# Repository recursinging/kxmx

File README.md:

# kxmx

kxmx, pronounced "krachmacher", is a moniker connecting a heterogenous, but loosely coupled group of projects, mostly having to do with audio and music.  In sum, the components should form a sort of musical instrument, or maybe better a "rig", but I don't consider that a design goal.

## Motivation

I'm in a band.  Actually, two.  I sing, not particularly good, but it's fun, and I enjoy making music.  What I enjoy more though, is learning about, and tinkering with the technical aspects of making music. Because of this, actual music composition or lyric writing can be regularly postponed for technical reasons.

Easily bored, I like to keep a diverse set of projects going parallel.  These projects may lie dormant for months. I work, I have kids, I don't have much me time.

## Parts, moving or otherwise

Here's a list of projects either already underway, or things I'd like to do eventually...

### kxmx_hirn

A robust, portable (but damn heavy) [DJ case](https://www.magma-bags.de/multi-format-workstation-xl-plus.html) which I gutted and hacked to support Eurorack modules with 350 HU of capacity.  Built in are +19v, +12v, -12v, and +5v power supplies. A lot of the other kxmx components are in, or destined for this case, but since there are a number of ideas I'd like to explore with the case itself, making it a project in it's own right.

### kxmx_erack

A set of basic PCB templates for Eurorack modules which leverage the wonder of exceptionally cheap chinese fabrication.

### [kxmx_ruitar](https://github.com/recursinging/ruitar)

A guitar shaped MIDI/OSC controller, and hopefully someday, a standalone synthesizer.  I wanted to make something tactile to control parameters with, but in a more familiar way (to me) Being more comfortable on the guitar than the keyboard, the ruitar is the logical solution.

### kxmx_trig

A piezo drum trigger module, intended to collect and send a few drum events to kxmx_hirn where they can be abused.

### kxmx_vl2

The brain of a lobotomized TC Helicon [Voice Live 2](https://www.tc-helicon.com/Categories/Tchelicon/Vocal/Multi-Effects/VOICELIVE-2/p/P0CMC) which has been converted from a foot pedal to Eurorack format mounted in kxmx_hirn

### kxmx_4x4

A 4x4 VCA matrix mixer based on SSM2164 clones, and has a modular design:

* *kxmx_4x4_core* - The 16 x2164 voltage control ports of the core module are intentionally broken out to the edge of the board. This allows for pluggable control boards to control the gain of the matrix however they want.  
* *kxmx_4x4_control_esp32* - This module controls the gain of the core using an Expressif ESP32 MCU which has WiFi and Bluetooth out of the box.  This module will make the mixer gain levels remotely controllable via MIDI or OSC.
* *kxmx_4x4_control_cv* - This module allows the gain of the core to be controlled by TRS jack at Eurorack CV levels.

### [kxmx_dsp](https://github.com/recursinging/kxmx_dsp)

Experiments with DSP concepts and algorithms

### [kxmx_trestle](https://github.com/recursinging/kxmx_trestle)

A bi-directional OSC SLIP encoded serial to UDP bridge.

## Licenses

I'll try to be consistent:

* Standalone software/firmware is [LGPLv3](https://www.gnu.org/licenses/lgpl-3.0.en.html)
* Software libraries are [MIT](https://opensource.org/licenses/MIT)
* Hardware/Media is [CC-BY-NC-SA 3.0](https://creativecommons.org/licenses/by-nc-sa/3.0/)

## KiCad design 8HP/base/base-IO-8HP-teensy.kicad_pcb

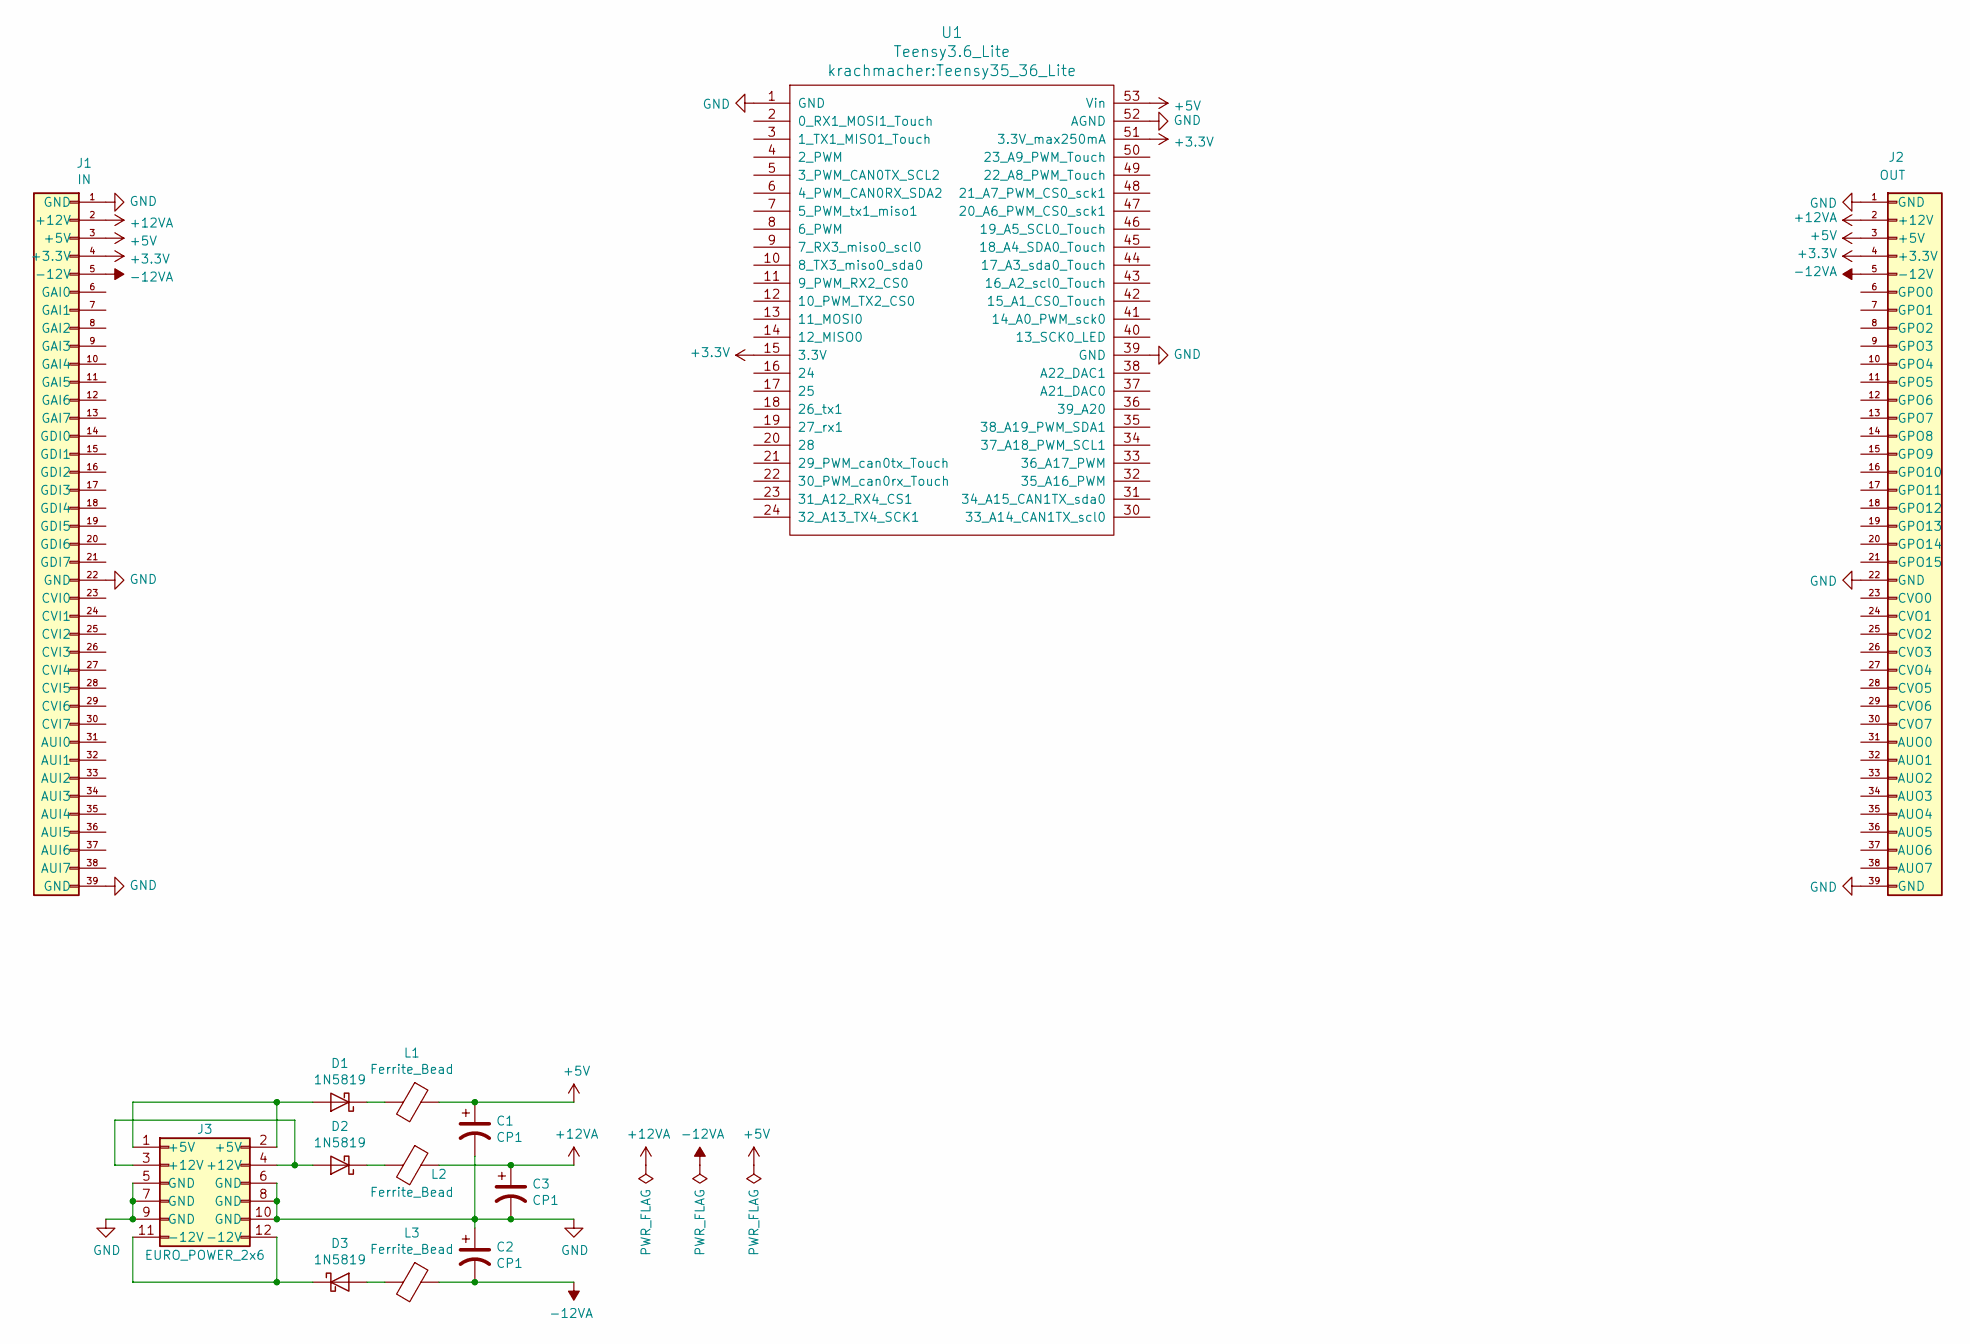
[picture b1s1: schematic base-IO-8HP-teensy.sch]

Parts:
C1, C2, C3: CP1; CP_Elec_4x5.8
D1, D2, D3: 1N5819; D_SOD-123
J1: IN; PinSocket39
J2: OUT; PinSocket39
J3: EURO_POWER_2x6; Pin_Header_Straight_2x06_Pitch2.54mm
L1, L2, L3: Ferrite_Bead; L_0603
U1: Teensy3.6_Lite; Teensy35_36_Lite

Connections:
+3V3: J1.4 (+3.3V), J2.4 (+3.3V), U1.15 (3.3V), U1.51 (3.3V_max250mA)
+5V: C1.1, J1.3 (+5V), J2.3 (+5V), L1.1, U1.53 (Vin)
+12VA: C3.1, J1.2 (+12V), J2.2 (+12V), L2.1
-12VA: C2.2, J1.5 (-12V), J2.5 (-12V), L3.1
GND: C1.2, C2.1, C3.2, J1.1 (GND), J1.22 (GND), J1.39 (GND), J2.1 (GND), J2.22 (GND), J2.39 (GND), J3.5 (GND), J3.6 (GND), J3.7 (GND), J3.8 (GND), J3.9 (GND), J3.10 (GND), U1.1 (GND), U1.39 (GND), U1.52 (AGND)
unnamed: D1.1 (K), L1.2
unnamed: D1.2 (A), J3.1 (+5V), J3.2 (+5V)
unnamed: D2.1 (K), L2.2
unnamed: D2.2 (A), J3.3 (+12V), J3.4 (+12V)
unnamed: D3.1 (K), J3.11 (-12V), J3.12 (-12V)
unnamed: D3.2 (A), L3.2

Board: 2 copper layers, 13 parts (2 on the bottom side), 11 nets, no tracks yet.

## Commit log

2018-02-06 Playing around with some ideas for a 14HP foundation
2018-02-07 Fix some bad dimensions
2018-02-14 Starting to standardize a few things
2018-02-15 Preliminary pin scheme...
2018-02-22 A little restructuring...
2018-02-22 Trying to figure out how to handle CV in best
2018-02-28 Rename the project
2018-02-28 We got the power
2018-03-08 Progress on the power supply
2018-03-14 Starting with the Teensy integration
2018-03-15 Add a simplified Teensy 3.6 symbol and footprint
2018-06-06 Add a few components
2018-08-29 Move the KiCAD project tree to a sub-folder
2018-08-31 Restructure. Rename. Document.
2021-03-03 Create CNAME
